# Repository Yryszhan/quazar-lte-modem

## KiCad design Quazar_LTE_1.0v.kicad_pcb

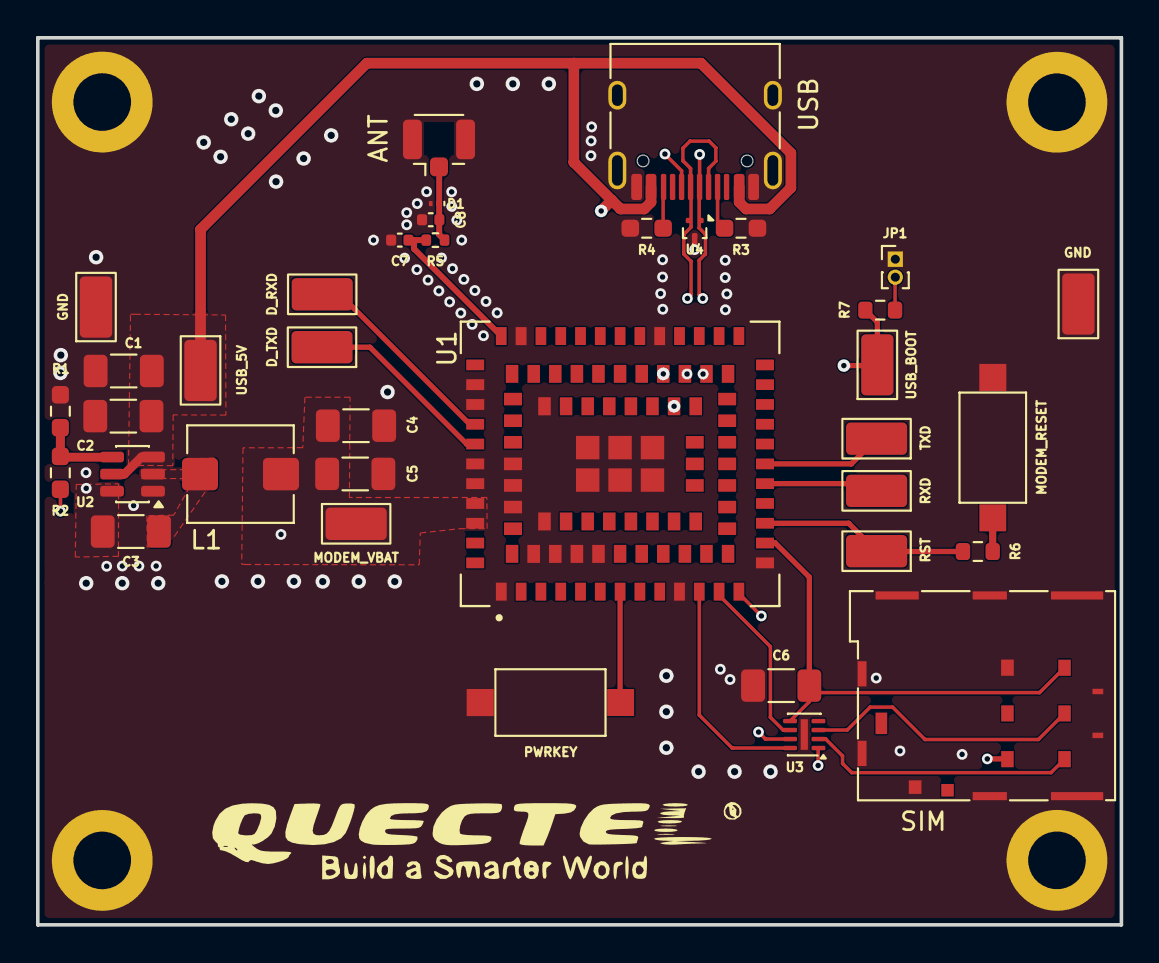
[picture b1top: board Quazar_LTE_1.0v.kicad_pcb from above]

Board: 4 copper layers, 60.2 x 49.3 mm, 41 parts (0 on the bottom side), 28 nets.

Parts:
ANT: Conn_Coaxial; U.FL_Hirose_U.FL-R-SMT-1_Vertical
C1: 10uf; C_1206_3216Metric_Pad1.33x1.80mm_HandSolder
C2, C3, C6: 100nf; C_1206_3216Metric_Pad1.33x1.80mm_HandSolder
C4, C5: 22uf; C_1206_3216Metric_Pad1.33x1.80mm_HandSolder
C7, C8: RF_MATCH_TBD; C_0402_1005Metric
D1: RF_ESD_TBD; Nexperia_DSN0603-2_0.6x0.3mm_P0.4mm
D_RXD: DBG_RXD; TestPoint_Keystone_5015_Micro_Mini
D_TXD: DBG_TXD; TestPoint_Keystone_5015_Micro_Mini
GND: GND; TestPoint_Keystone_5015_Micro_Mini
GND#2: GND; TestPoint_Keystone_5015_Micro_Mini
H1, H2, H3, H4: MountingHole_Pad; MountingHole_3.2mm_M3_DIN965_Pad
JP1: Jumper_2_Open; PinHeader_1x02_P1.00mm_Vertical
L1: 6.8uH; L_Bourns_SRP5030T
R1: 10 kΩ; R_0603_1608Metric_Pad0.98x0.95mm_HandSolder
R2: 53,3 kΩ; R_0603_1608Metric_Pad0.98x0.95mm_HandSolder
R3, R4: 5.1k; R_0603_1608Metric_Pad0.98x0.95mm_HandSolder
R5: 0R; R_0402_1005Metric
R6: 1K; R_0603_1608Metric
R7: 4.7k; R_0603_1608Metric
RST: TP_RESET; TestPoint_Keystone_5015_Micro_Mini
RXD: MAIN_RXD; TestPoint_Keystone_5015_Micro_Mini
SIM: JAE_SIM_Card_SF72S006
SW1: PWRKEY; SW_SPST_CK_RS282G05A3
SW2: MODEM_RESET; SW_SPST_CK_RS282G05A3
TP2: MODEM_VBAT; TestPoint_Keystone_5015_Micro_Mini
TXD: MAIN_TXD; TestPoint_Keystone_5015_Micro_Mini
U1: EG810MEULA-I05-SNNSA; XDCR_EG810MEULA-I05-SNNSA
U2: LMR51430; SOT-23-6
U3: TPD3F303DPV; Texas_R-PUSON-N8_USON-8-1EP_1.6x2.1mm_P0.5mm_EP0.4x1.7mm
U4: TPD2EUSB30; Texas_DRT-3
USB: USB_C_Receptacle_USB2.0_16P; USB_C_Receptacle_HRO_TYPE-C-31-M-12
USB_5V: USB_5V; TestPoint_Keystone_5015_Micro_Mini
USB_BOOT: USB_BOOT; TestPoint_Keystone_5015_Micro_Mini

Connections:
/DEBUG/PWRKEY: SW1.1, U1.7 (PWRKEY)
/DEBUG/RESET_N: R6.1, RST.1 (1_1), U1.15 (~RESET)
/DEBUG/USB_BOOT: R7.2, U1.82 (USB_BOOT), USB_BOOT.1 (1_1)
/LTE_module/USB_D_N: U1.60 (USB_DM), U4.2 (D-), USB.A7 (D-), USB.B7 (D-)
/LTE_module/USB_D_P: U1.59 (USB_DP), U4.1 (D+), USB.A6 (D+), USB.B6 (D+)
/LTE_module/USB_VBUS_SENSE: C1.2, C2.1, U1.61 (USB_VBUS), U2.3 (VIN), U2.5 (EN), USB.A4 (VBUS), USB.A9 (VBUS), USB.B4 (VBUS), USB.B9 (VBUS), USB_5V.1 (1_1)
/LTE_module/USIM1_CLK: U1.13 (USIM1_CLK), U3.7 (CLK_IN)
/LTE_module/USIM1_DATA: U1.11 (USIM1_DATA), U3.8 (DATA1_IN)
/LTE_module/USIM1_RST: U1.12 (USIM1_RST), U3.6 (DATA2_IN)
/LTE_module/USIM1_VDD: C6.2, SIM.C1 (VCC), U1.14 (USIM1_VDD), U3.5 (V_{CC})
GND: ANT.2 (Ext), C1.1, C2.2, C4.1, C5.2, C6.1, C7.2, C8.2, D1.2 (A2), GND.1 (1_1), GND#2.1 (1_1), H1.1 (1_1), H2.1 (1_1), H3.1 (1_1), H4.1 (1_1), JP1.1 (A), R1.2, R3.2, R4.1, SIM.C5 (GND), SIM.SH, SW1.2, SW2.2, U1.1 (GND), U1.10 (GND), U1.27 (GND), U1.34 (GND), U1.36 (GND), U1.37 (GND), U1.40 (GND), U1.41 (GND), U1.45 (GND), U1.46 (GND), U1.47 (GND), U1.48 (GND), U1.70 (GND), U1.71 (GND), U1.72 (GND), U1.73 (GND), U1.88 (GND), U1.89 (GND), U1.90 (GND), U1.91 (GND), U1.92 (GND), U1.93 (GND), U1.94 (GND), U1.95 (GND), U2.1 (GND), U3.9 (GND), U4.3 (GND), USB.A1 (GND), USB.A12 (GND), USB.B1 (GND), USB.B12 (GND), USB.SH (SHIELD)
unnamed: ANT.1 (In), C8.1, D1.1 (A1), R5.1
unnamed: SIM.C3 (CLK), U3.2 (CLK_OUT)
unnamed: SIM.C7 (I/O), U3.1 (DATA1_OUT)
unnamed: SIM.C2 (RST), U3.3 (DATA2_OUT)
unnamed: R3.1, USB.A5 (CC1)
unnamed: R4.2, USB.B5 (CC2)
unnamed: JP1.2 (B), R7.1
unnamed: R6.2, SW2.1
unnamed: C7.1, R5.2, U1.35 (ANT_MAIN)
unnamed: D_RXD.1 (1_1), U1.38 (DBG_RXD)
unnamed: D_TXD.1 (1_1), U1.39 (DBG_TXD)
unnamed: RXD.1 (1_1), U1.17 (MAIN_RXD)
unnamed: TXD.1 (1_1), U1.18 (MAIN_TXD)
unnamed: C3.1, U2.6 (CB)
unnamed: R1.1, R2.2, U2.4 (FB)
unnamed: C3.2, L1.1, U2.2 (SW)
VBAT: C4.2, C5.1, L1.2, R2.1, TP2.1 (1_1), U1.42 (VBAT), U1.43 (VBAT)
